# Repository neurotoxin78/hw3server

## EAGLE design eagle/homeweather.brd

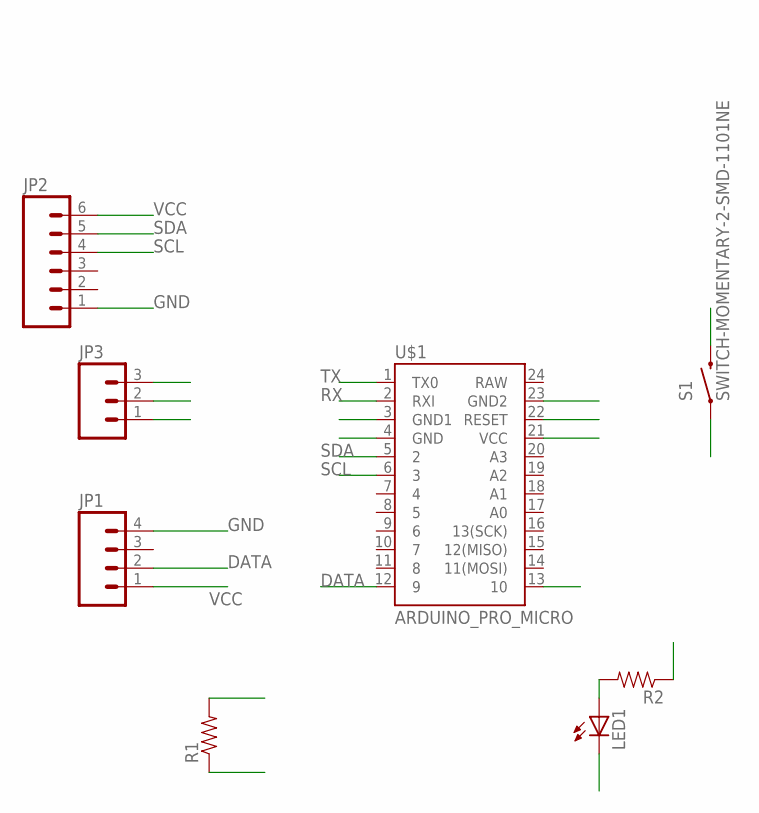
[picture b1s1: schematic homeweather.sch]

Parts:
JP1: M04PTH; 1X04
JP2: M06SIP; 1X06
JP3: M03PTH; 1X03
LED1: LED3MM
R1, R2: RESISTOR0805-RES; 0805
S1: SWITCH-MOMENTARY-2-SMD-1101NE; TACTILE-SWITCH-1101NE
U$1: ARDUINO_PRO_MICRO

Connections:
DATA: JP1.2, R1.2, U$1.12 (9)
GND: JP1.4, JP2.1, JP3.1, LED1.K (C), S1.P$1 (1), U$1.3 (GND1), U$1.4 (GND), U$1.23 (GND2)
LED1: R2.1, U$1.13 (10)
unnamed: LED1.A, R2.2
RESET: S1.P$2 (2), U$1.22 (RESET)
RX: JP3.2, U$1.2 (RXI)
SCL: JP2.4, U$1.6 (3)
SDA: JP2.5, U$1.5 (2)
TX: JP3.3, U$1.1 (TX0)
VCC: JP1.1, JP2.6, R1.1, U$1.21 (VCC)

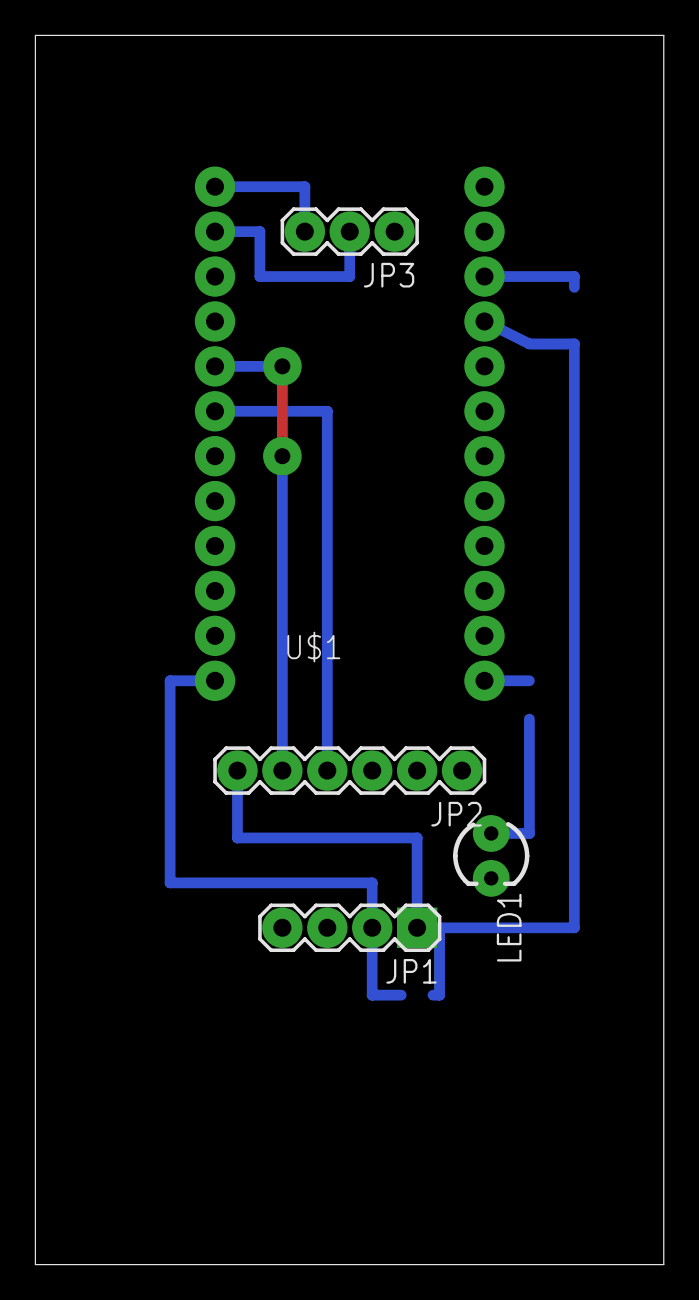
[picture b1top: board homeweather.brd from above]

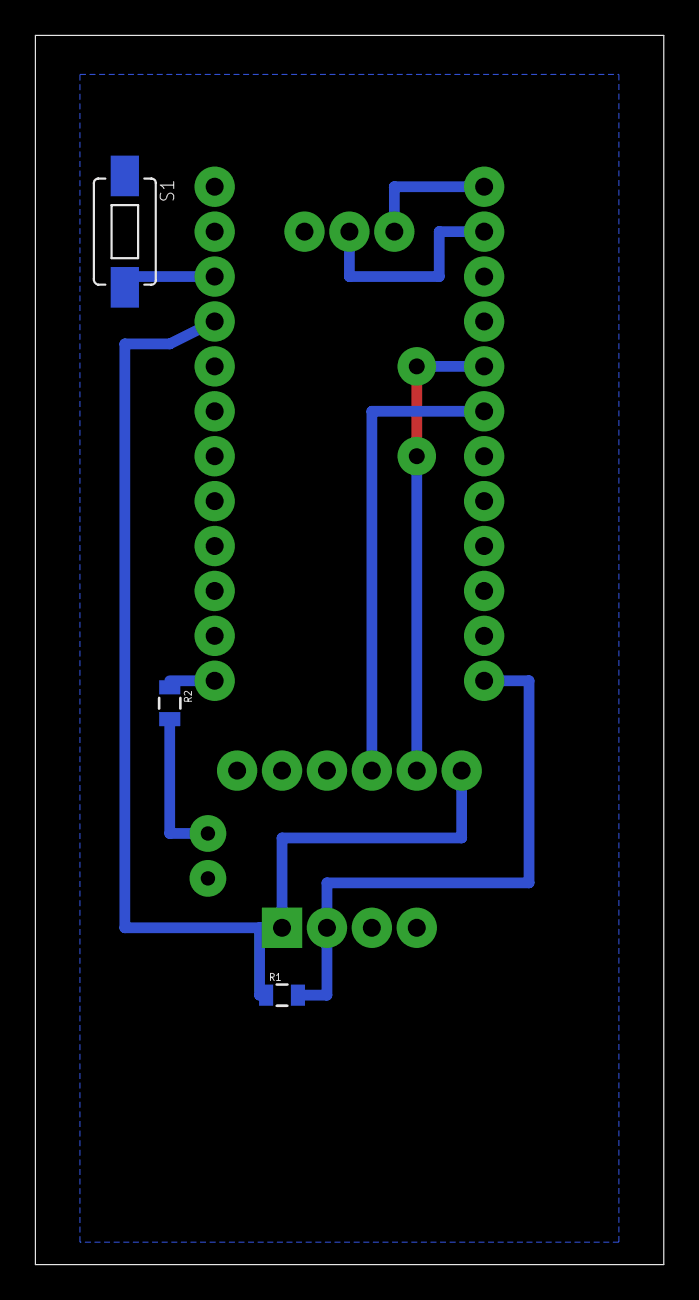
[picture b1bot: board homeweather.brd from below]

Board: 2 copper layers, 35.5 x 69.5 mm, 8 parts (3 on the bottom side), 10 nets.

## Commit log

2014-02-20 Add all
    OB
2014-02-20 add Eagle Schematics and Board

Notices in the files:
parts and their libraries:
SparkFun-Boards: Licensing: CC v3.0 Share-Alike You are welcome to use this library for commercial purposes.
